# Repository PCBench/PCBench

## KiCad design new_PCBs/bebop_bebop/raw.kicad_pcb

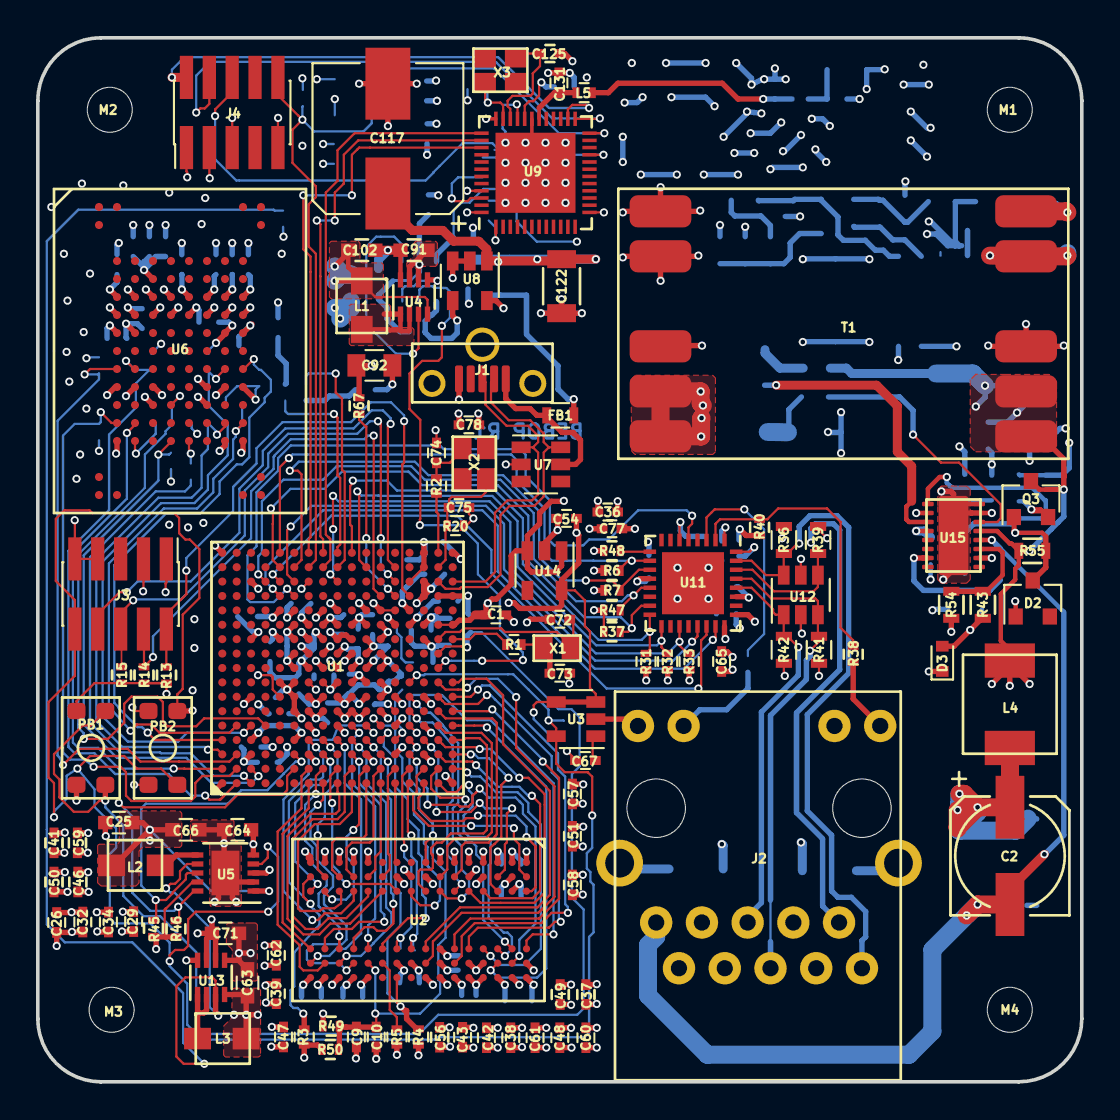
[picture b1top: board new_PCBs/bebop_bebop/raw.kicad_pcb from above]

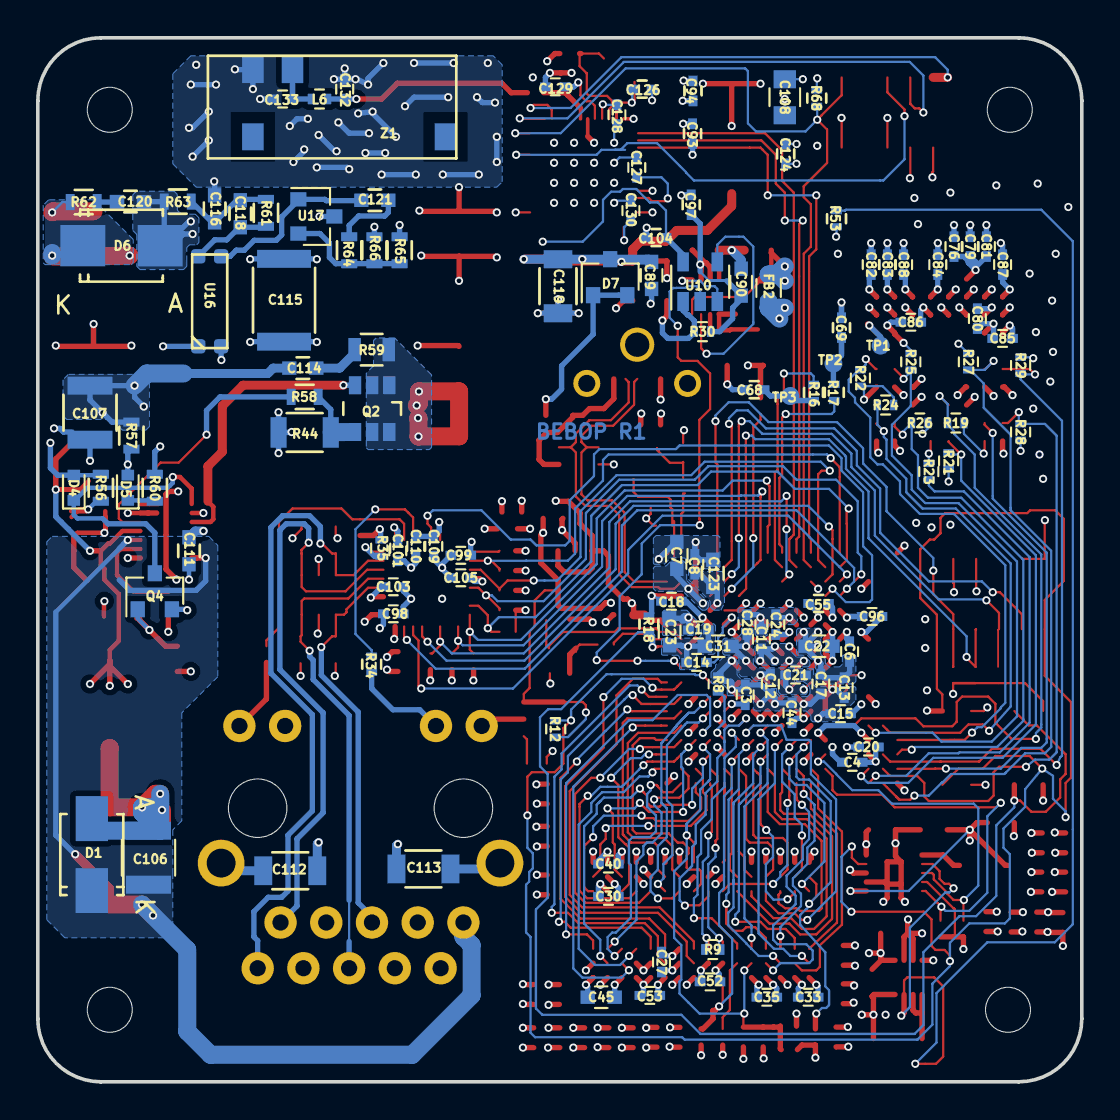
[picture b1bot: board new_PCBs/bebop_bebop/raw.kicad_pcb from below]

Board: 4 copper layers, 58.0 x 58.0 mm, 245 parts (128 on the bottom side), 175 nets.

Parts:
C1, C3, C4, C6, C8, C9, C10, C11, C12, C13, C14, C15, C17, C18, C19, C20, C21, C24, C26, C27, C28, C29, C30, C32, C33, C34, C35, C36, C37, C38, C39, C40, C41, C42, C43, C44, C46, C47, C48, C49, C50, C51, C52, C53, C54, C55, C56, C57, C58, C59, C60, C61, C62, C65, C76, C77, C78, C79, C80, C81, C82, C83, C84, C85, C86, C87, C88, C93, C94, C96, C97, C98, C99, C101, C103, C104, C105, C109, C110, C124, C127: C0402_1u_10Vdc_X5R; C_0402
C2: PCAP_220u_15; c_elec_6.3x7.7
C7, C22, C23, C25, C31, C45: C0603_22u_10Vdc_X5R; C_0603
C63, C64, C66, C71, C91, C102, C123: C0603_10u_10Vdc_X7R; C_0603
C67: C0402_100n_100Vdc_X5R; C_0402
C68, C69: C0402_10n_50Vdc_X7R; C_0402
C72, C73, C74, C75, C125, C126: C0402_15p_100Vdc_C0G; C_0402
C89, C90: C0603_1u_25Vdc_X7R; C_0603
C92: C0805_10u_25Vdc_X7R; C_0805
C106, C107: C1210_1u_100Vdc_X7R; C_1210
C108: C0805_20n_50Vdc_X7R; C_0805
C111: C0603_4u7_10Vdc_X7R; C_0603
C112, C113: C1206_1n5_1000Vdc_X7R; C_1206
C114: C0603_68p_200Vdc_X7R; C_0603
C115: C1812_2n2_250Vac_X7R; C_1812
C116: C0603_1u_10Vdc_X7R; C_0603
C117: PCAP_220u_15; CP_Elec_8x5.4
C118: C0603_33n_16Vdc_X7R; C_0603
C119, C122: C1206_100u_6.3Vdc_X5R; C_1206
C120: C0603_470p_100Vdc_X7R; C_0603
C121: C0603_27n_16Vdc_X7R; C_0603
C128, C129: C0402_100p_25Vdc_C0G; C_0402
C130: C0402_100n_10Vdc_X7R; C_0402
C131: C0402_0p8_25Vdc_C0G_5; C_0402
C132, C133: C0402_0p8_50Vdc_C0G_3; C_0402
D1: SMAJ58A; SMA_Standard
D2: BZX84C8V2LT1G; SOT-23
D3, D4, D5: BAS516,135; D_SOD-523
D6: P6SMB540A_E3_52; SMB_Standard
D7: BAT54C-7-F; SOT-23
FB1, FB2: BL0603_BLM18KG121TN1D; R_0603
J1: 1051330011
J2: 7499210123
J3, J4: FTSH-105-01-F-DV-K
L1, L3: IHLP1212_1u_1; IHLP1212
L2: IHLP1212_3u3_a5; IHLP1212
L4: IHLP2020_3u3_13; IHLP2020
L5: LQG15HN_3n9; L_0402
L6: LQG15HN_2n7; L_0402
M1, M2, M3, M4: MHNP_2.5mm; MH_2.5mm
PB1, PB2: KMR631NGULCLFS; kmr6
Q2: Si3440ADV; TSOT-6-MK06A
Q3: MMBTA42; SOT-23
Q4: 2N7002; SOT-23
R1, R2, R9, R16, R17: R0402_100R; R_0402
R3, R4, R18, R19, R21, R22, R24, R25, R26, R27, R28, R29, R53, R68: R0402_46k40; R_0402
R5, R8: R0402_240R; R_0402
R6, R7, R12, R30, R33, R37, R40, R45, R46, R47, R48: R0402_10k; R_0402
R13, R14, R15, R67: R0402_100k; R_0402
R20: R0402_2M20; R_0402
R23: R0402_22R; R_0402
R31, R32, R49, R50: R0402_1k50; R_0402
R34, R38: R0402_330R; R_0402
R35: R0402_12k10; R_0402
R36, R39, R41, R42: R0603_49R90; R_0603
R43: R0603_10k; R_0603
R44: R1206_0R130; R_1206
R54, R65: R0603_100k; R_0603
R55, R57: R0603_220k; R_0603
R56: R0603_6k80; R_0603
R58: R0603_4k70; R_0603
R59: R0805_100R_126mW; R_0805
R60: R0603_510R; R_0603
R61: R0603_1k; R_0603
R62: R0603_10R; R_0603
R63: R0603_470R; R_0603
R64: R0603_47k; R_0603
R66: R0603_33k20; R_0603
T1: POE60F-50L_; POE60F
TP1, TP2, TP3: TP; TP_1mm
U1: MCIMX6G2AVM07; LFBGA289
U2: MT41K512M16HA-125; BGA-96_pitch0.8mm_dia0.4mm
U3: LP3470M5-3.08; SOT-23-5
U4: MIC23150-SYMT; DFN-8_2x2mm_Pitch0.5mm
U5: LTC3447; DFN-10-1EP_3x3mm_Pitch0.5mm
U6: FEMC004GTTE7-T13-17; 100LBGA_DQ
U7, U12: USBLC6-4; SOT-23-6
U8: NCP360SNAET1G; SOT-23-5
U9: nRF52832; UQFN-48-1EP_6x6mm_Pitch0.4mm
U10: SN74AHC1G08; SOT-23-5
U11: LAN8710; QFN-32-1EP_5x5mm_Pitch0.5mm
U13: MIC23150-55YMT; DFN-8_2x2mm_Pitch0.5mm
U14: NCV551SN33T1G; SOT-23-5
U15: LTC4267IDHC; DHC16
U16: PS2911-1e; PS2911
U17: TL431BSA-7; SOT-23
X1: NX2012SA-32.768K-STD-MUB-1; NX2012
X2: NX2520SA-24.000000MHZ; NX2520
X3: NX2520SA-32.000000MHZ; NX2520
Z1: PRO-OB-440

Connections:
/BLE/BM: U1.G17, U9.39
/BLE/NRF_SWDCLK: J4.4, U9.25
/BLE/NRF_SWDIO: J4.2, U9.26
/BLE/NRF_SWO: J4.6, U9.21
/BLE/RESET_N: J4.10, R68.2, U1.G16, U9.24
/CPU/A0: U1.L5, U2.N3
/CPU/A1: U1.H2, U2.P7
/CPU/A2: U1.K1, U2.P3
/CPU/A3: U1.M2, U2.N2
/CPU/A4: U1.K4, U2.P8
/CPU/A5: U1.L1, U2.P2
/CPU/A6: U1.G2, U2.R8
/CPU/A7: U1.H4, U2.R2
/CPU/A8: U1.J4, U2.T8
/CPU/A9: U1.L2, U2.R3
/CPU/A10: U1.M4, U2.L7
/CPU/A11: U1.K3, U2.R7
/CPU/A12: U1.L4, U2.N7
/CPU/A13: U1.H3, U2.T3
/CPU/A14: U1.G1, U2.T7
/CPU/A15: U1.K5, U2.M7
/CPU/BM0: PB1.2, R18.1, U1.T10
/CPU/DQ0: U1.T4, U2.E3
/CPU/DQ1: U1.U6, U2.F7
/CPU/DQ2: U1.T6, U2.F2
/CPU/DQ3: U1.U7, U2.F8
/CPU/DQ4: U1.U8, U2.H7
/CPU/DQ5: U1.T8, U2.H8
/CPU/DQ6: U1.T5, U2.G2
/CPU/DQ7: U1.U4, U2.H3
/CPU/DQ8: U1.U2, U2.D7
/CPU/DQ9: U1.U3, U2.C3
/CPU/DQ10: U1.U5, U2.C8
/CPU/DQ11: U1.R4, U2.C2
/CPU/DQ12: U1.P5, U2.A7
/CPU/DQ13: U1.P3, U2.B8
/CPU/DQ14: U1.R2, U2.A2
/CPU/DQ15: U1.R1, U2.A3
/CPU/DRAM_CAS_B: U1.J2, U2.K3
/CPU/DRAM_CS0_B: U1.N2, U2.L2
/CPU/DRAM_DQM0: U1.T7, U2.E7
/CPU/DRAM_DQM1: U1.T3, U2.D3
/CPU/DRAM_ODT0: U1.N1, U2.K1
/CPU/DRAM_RAS_B: U1.M5, U2.J3
/CPU/DRAM_RESET: R3.1, U1.G4, U2.T2
/CPU/DRAM_SDBA0: U1.M1, U2.M2
/CPU/DRAM_SDBA1: U1.H1, U2.N8
/CPU/DRAM_SDBA2: U1.K2, U2.M3
/CPU/DRAM_SDCKE0: R4.1, U1.M3, U2.K9
/CPU/DRAM_SDCLK0_N: R9.1, U1.P2, U2.K7
/CPU/DRAM_SDCLK0_P: R9.2, U1.P1, U2.J7
/CPU/DRAM_SDQS0_N: U1.P7, U2.G3
/CPU/DRAM_SDQS0_P: U1.P6, U2.F3
/CPU/DRAM_SDQS1_N: U1.T2, U2.B7
/CPU/DRAM_SDQS1_P: U1.T1, U2.C7
/CPU/DRAM_SDWE_B: U1.J1, U2.L3
/CPU/DRAM_VREFDQ: C9.2, C10.1, R49.2, R50.1, U1.P4, U2.H1, U2.M8
/CPU/DRAM_ZQ0: R5.1, U2.L8
/CPU/DRAM_ZQPAD: R8.1, U1.N4
/CPU/DRX: R16.2, U1.J16
/CPU/DTX: R17.2, U1.J17
/CPU/I2C2_SCL: R45.2, U1.F3, U5.8
/CPU/I2C2_SDA: R46.2, U1.F2, U5.10
/CPU/JTAG_TCK: J3.4, R14.2, U1.M14
/CPU/JTAG_TDI: J3.8, U1.N16
/CPU/JTAG_TDO: J3.6, R15.2, U1.N15
/CPU/JTAG_TMS: J3.2, R13.2, U1.P14
/CPU/JTAG_TRST_N: R67.2, U1.N14
/CPU/NVCC_PLL: C8.1, C123.1, U1.P13
/CPU/P3V3_PG: R53.2, U5.7, U13.3
/CPU/POWER_REQ: U1.T9, U10.2
/CPU/RST_N: J3.10, PB2.2, R12.2, U1.P8, U3.5, U5.4
/CPU/UART3_RX_DATA: U1.H16, U9.37
/CPU/UART3_TX_DATA: U1.H17, U9.38
/CPU/VDD_ARM_CAP: C6.1, C13.1, C17.1, C22.1, U1.G9, U1.G10, U1.G11, U1.H11
/CPU/VDD_HIGH_CAP: C3.1, C7.1, U1.N6, U1.R14, U1.R15
/CPU/VDD_SNVS_CAP: C14.1, U1.N12
/CPU/VDD_SOC_CAP: C12.1, C21.1, C24.1, C28.1, C31.1, U1.G8, U1.H8, U1.J8, U1.J11, U1.K8, U1.K11, U1.L8, U1.L9, U1.L10, U1.L11
/CPU/VDD_USB_CAP: C19.1, C23.1, U1.R12
/CPU/eMMC_CLK: R23.2, U1.C1
/CPU/eMMC_CLK_2: R23.1, U6.P6
/CPU/eMMC_CMD: R21.2, U1.C2, U6.P5
/CPU/eMMC_D0: R29.2, U1.B3, U6.K2
/CPU/eMMC_D1: R28.2, U1.B2, U6.N2
/CPU/eMMC_D2: R27.2, U1.B1, U6.K3
/CPU/eMMC_D3: U1.A2, U6.N3
/CPU/eMMC_D4: R26.2, U1.A3, U6.N8
/CPU/eMMC_D5: R25.2, U1.C5, U6.K8
/CPU/eMMC_D6: R24.2, U1.B5, U6.N9
/CPU/eMMC_D7: R22.2, U1.A4, U6.K9
/CPU/eMMC_RST_N: R19.2, U1.D5, U6.M5
/CPU/eMMC_VDDIM: C76.1, C79.1, C81.1, U6.E4
/CR: C109.1, C110.1, U11.6
/ENET_CLK: U1.F14, U11.5
/ENET_CRS_DV: R37.2, U1.E16, U11.15
/ENET_MDC: R32.1, U1.L16, U11.17
/ENET_MDIO: R31.1, U1.K17, U11.16
/ENET_RST_N: R33.1, U1.J15, U11.19
/ENET_RXD0: R7.2, U1.F16, U11.11
/ENET_RXD1: R6.2, U1.E17, U11.10
/ENET_RXER: R47.2, U1.D15, U11.13
/ENET_TXD0: U1.E15, U11.22
/ENET_TXD1: U1.E14, U11.23
/ENET_TXEN: U1.F15, U11.21
/P3V3_EN: U4.3, U10.4
/PoE/NGATE: Q2.3, U15.3
/PoE/PVCC: C111.2, D5.2, Q3.2, R54.1, R56.2, R57.2, U15.4
/PoE/SENSE: R58.2, U15.14
/PoE/VPORTN: C2.2, C106.1, D1.1, J2.10, U15.7, U15.12
/PoE/VPORTP: C2.1, C106.2, D1.3, J2.9, L4.1
/USB_D_N: J1.2, U1.T15, U7.6
/USB_D_P: J1.3, U1.U15, U7.1
/USB_VBUS: FB1.1, J1.1, U7.5
/USB_VBUS_2: C89.1, C117.1, C119.1, C120.1, C122.1, D6.2, D7.3, R63.1, R65.1, U8.1
GND: C1.2, C3.2, C4.2, C6.2, C7.2, C8.2, C10.2, C11.2, C12.2, C13.2, C14.2, C15.2, C17.2, C18.2, C19.2, C20.2, C21.2, C22.2, C23.2, C24.2, C25.2, C26.2, C27.2, C28.2, C29.2, C30.2, C31.2, C32.2, C33.2, C34.2, C35.2, C36.2, C37.2, C38.2, C39.2, C40.2, C41.2, C42.2, C43.2, C44.2, C45.2, C46.2, C47.2, C48.2, C49.2, C50.2, C51.2, C52.2, C53.2, C54.2, C55.2, C56.2, C57.2, C58.2, C59.2, C60.2, C61.2, C62.2, C63.2, C64.2, C65.2, C66.2, C67.2, C68.2, C69.2, C71.2, C72.2, C73.2, C74.2, C75.2, C76.2, C77.2, C78.2, C79.2, C80.2, C81.2, C82.2, C83.2, C84.2, C85.2, C86.2, C87.2, C88.2, C89.2, C90.2, C91.2, C92.2, C93.2, C94.2, C96.2, C97.2, C98.2, C99.2, C101.2, C102.2, C103.2, C104.2, C105.2, C108.2, C109.2, C110.2, C112.2, C113.2, C115.1, C116.2, C117.2, C119.2, C122.2, C123.2, C124.2, C125.1, C126.1, C127.2, C128.2, C129.2, C130.2, C131.2, C132.2, C133.2, J1.5, J1.6, J1.7, J1.8, J2.12, J2.14, J3.3, J3.7, J3.9, J4.3, J4.5, J4.9, PB2.1, R3.2, R4.2, R5.2, R8.2, R18.2, R20.2, R33.2, R35.2, R40.2, R50.2, R66.2, T1.7, T1.8, TP1.1, U1.A1, U1.A17, U1.C3, U1.C7, U1.C11, U1.C15, U1.E8, U1.E11, U1.F6, U1.F7, U1.F8, U1.F9, U1.F10, U1.F11, U1.F12, U1.G3, U1.G5, U1.G7, U1.G12, U1.G15, U1.H7, U1.H12, U1.J5, U1.J7, U1.J12, U1.K7, U1.K12, U1.L3, U1.L7, U1.L12, U1.M7, U1.M8, U1.M9, U1.M10, U1.M11, U1.M12, U1.N3, U1.N5, U1.N7, U1.P15, U1.R3, U1.R5, U1.R7, U1.R11, U1.R16, U1.R17, U1.T14, U1.U1, U1.U14, U1.U17, U2.A9, U2.B1, U2.B3, U2.B9, U2.D1, U2.D8, U2.E1, U2.E2, U2.E8, U2.F9, U2.G1, U2.G8, U2.G9, U2.J2, U2.J8, U2.M1, U2.M9, U2.P1, U2.P9, U2.T1, U2.T9, U3.2, U4.5, U4.8, U5.2, U5.11, U6.G2, U6.G3, U6.G4, U6.G5, U6.G6, U6.G7, U6.G8, U6.G9, U6.H2, U6.H9, U6.L3, U6.L8, U6.M4, U6.M7, U6.P2, U6.P9, U7.2, U8.2, U8.3, U9.31, U9.45, U9.49, U10.3, U11.24, U11.25, U11.33, U12.2, U13.5, U13.8, U14.2, U17.3, Z1.1
GND_POWER: C107.1, C111.1, C115.2, D2.1, D3.1, Q4.2, R44.2, T1.3, U15.2, U15.10, U15.15, U15.16, U15.17, U16.2
unnamed: C67.1, U3.1
unnamed: C68.1, R16.1, TP3.1
unnamed: C69.1, R17.1, TP2.1
unnamed: C72.1, U1.T11, X1.1
unnamed: C73.1, R1.2, X1.3
unnamed: C74.1, R2.2, X2.1
unnamed: C75.1, R20.1, U1.T16, X2.3
unnamed: C102.1, FB2.1, L1.2, U4.4
unnamed: C107.2, C114.1, L4.2, Q3.3, R55.2, R57.1, T1.1, T1.2, U15.13
unnamed: C112.1, J2.15
unnamed: C113.1, J2.16
unnamed: C114.2, R59.2
unnamed: C116.1, C118.1, R61.1, R63.2
unnamed: C118.2, R61.2, U16.4
unnamed: C120.2, R62.2
unnamed: C121.1, R64.2
unnamed: C121.2, U16.3, U17.1
unnamed: C125.2, U9.34, X3.3
unnamed: C126.2, U9.35, X3.1
unnamed: C127.1, U9.46
unnamed: C128.1, U9.33
unnamed: C129.1, U9.32
unnamed: C130.1, U9.1
unnamed: C131.1, L5.1, U9.30
unnamed: C132.1, L5.2, L6.1
unnamed: C133.1, L6.2, Z1.2
unnamed: D2.3, Q3.1, R55.1
unnamed: D3.2, Q4.1, R43.1
unnamed: D4.1, Q4.3, U15.1
unnamed: D4.2, R56.1, U16.1
unnamed: D5.1, R60.2
unnamed: D6.1, R62.1, T1.5, T1.6
unnamed: D7.1, D7.2, FB1.2
unnamed: J2.1, R36.2, U11.31, U12.6
unnamed: J2.2, R39.2, U11.30, U12.4
unnamed: J2.5, R41.2, U11.29, U12.3
unnamed: J2.6, R42.2, U11.28, U12.1
unnamed: J2.11, R38.2
unnamed: J2.13, R34.2
unnamed: L1.1, U4.1, U4.2
unnamed: L2.2, U5.6
unnamed: L3.2, U13.1, U13.2
unnamed: Q2.1, Q2.2, Q2.5, Q2.6, R59.1, T1.11, T1.12
unnamed: Q2.4, R44.1, R58.1
unnamed: R1.1, U1.U11
unnamed: R2.1, U1.T17
unnamed: R30.2, U8.4, U10.1
unnamed: R34.1, U11.3
unnamed: R35.1, U11.32
unnamed: R38.1, R40.1, U11.2
unnamed: R43.2, R54.2, U15.11
unnamed: R48.2, U11.9
unnamed: R60.1, T1.10
unnamed: R64.1, R65.2, R66.1, U17.2
P1V4: C4.1, C11.1, C15.1, C20.1, C25.1, C66.1, L2.1, U1.H9, U1.H10, U1.J9, U1.J10, U1.K9, U1.K10, U5.1
P1V35: C9.1, C27.1, C30.1, C33.1, C35.1, C37.1, C38.1, C39.1, C40.1, C42.1, C43.1, C44.1, C45.1, C47.1, C48.1, C49.1, C51.1, C52.1, C53.1, C56.1, C57.1, C58.1, C60.1, C61.1, C62.1, C63.1, L3.1, R49.1, U1.G6, U1.H6, U1.J6, U1.K6, U1.L6, U1.M6, U2.A1, U2.A8, U2.B2, U2.C1, U2.C9, U2.D2, U2.D9, U2.E9, U2.F1, U2.G7, U2.H2, U2.H9, U2.K2, U2.K8, U2.N1, U2.N9, U2.R1, U2.R9, U13.4
P3V3: C26.1, C29.1, C32.1, C34.1, C36.1, C41.1, C46.1, C50.1, C55.1, C59.1, C64.1, C65.1, C71.1, C77.1, C78.1, C80.1, C82.1, C83.1, C84.1, C85.1, C86.1, C87.1, C88.1, C92.1, C93.1, C94.1, C96.1, C98.1, C99.1, C101.1, C103.1, C105.1, C108.1, C124.1, FB2.2, J2.3, J2.4, J3.1, J4.1, PB1.1, R6.1, R7.1, R13.1, R14.1, R15.1, R19.1, R21.1, R22.1, R24.1, R25.1, R26.1, R27.1, R28.1, R29.1, R31.2, R32.2, R36.1, R37.1, R39.1, R41.1, R42.1, R45.1, R46.1, R47.1, R48.1, R53.1, R67.1, R68.1, U1.C4, U1.E7, U1.E13, U1.F4, U1.F13, U1.H13, U1.J13, U1.L13, U1.M13, U1.N13, U5.3, U5.5, U5.9, U6.F2, U6.F3, U6.F4, U6.F5, U6.F6, U6.F7, U6.F8, U6.F9, U6.H3, U6.H8, U6.L2, U6.L4, U6.L7, U6.L9, U6.P3, U6.P8, U9.13, U9.36, U9.48, U11.1, U11.12, U11.27, U12.5, U13.6, U13.7
P3V3_PERM: C18.1, C54.1, C104.1, R12.1, U1.P12, U3.3, U3.4, U10.5, U14.5
P5V0: C1.1, C90.1, C91.1, C97.1, R30.1, U1.T12, U1.U12, U4.6, U4.7, U8.5, U14.1, U14.3

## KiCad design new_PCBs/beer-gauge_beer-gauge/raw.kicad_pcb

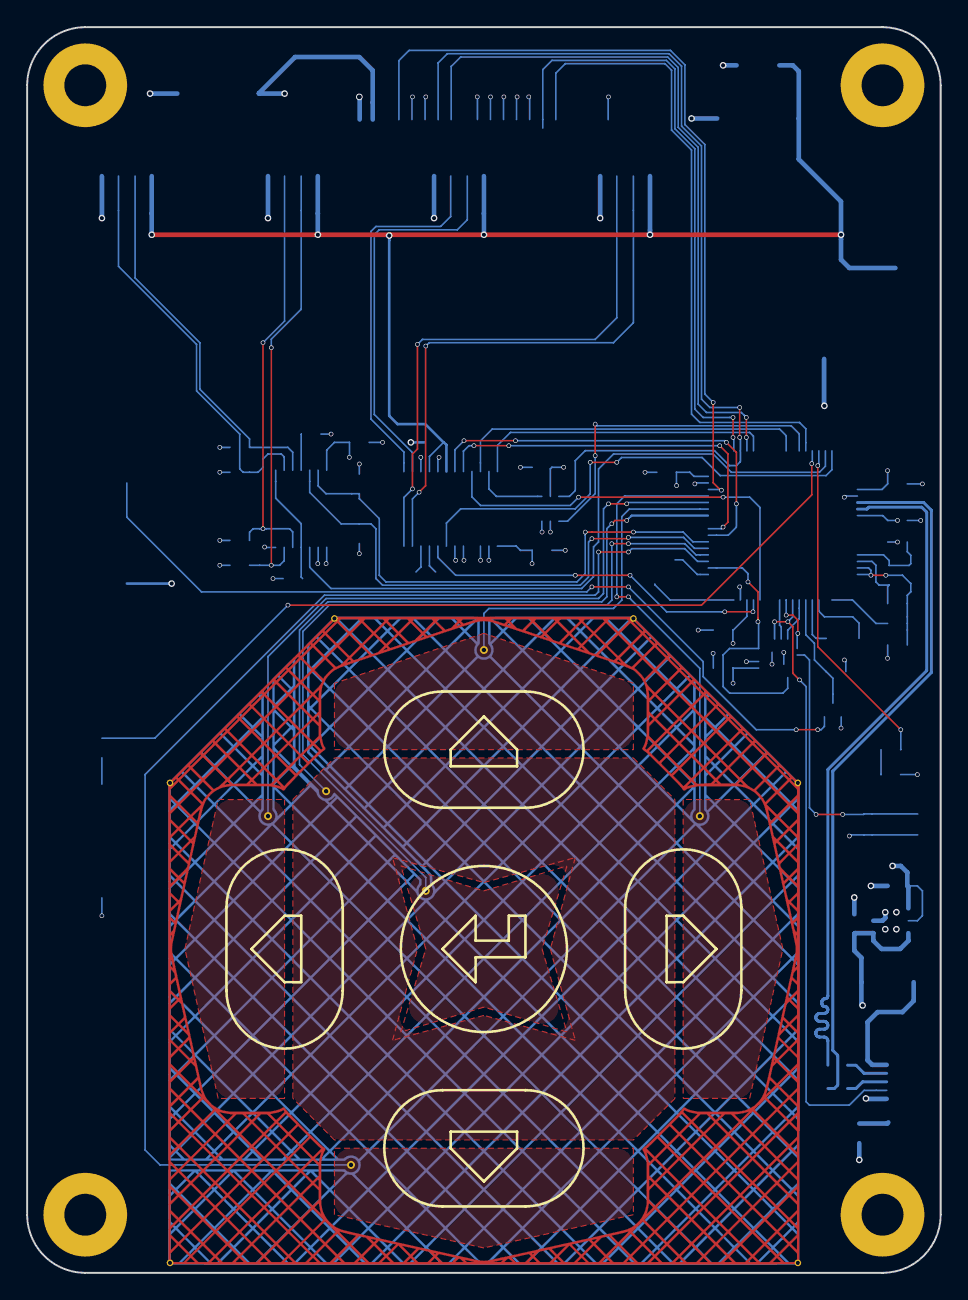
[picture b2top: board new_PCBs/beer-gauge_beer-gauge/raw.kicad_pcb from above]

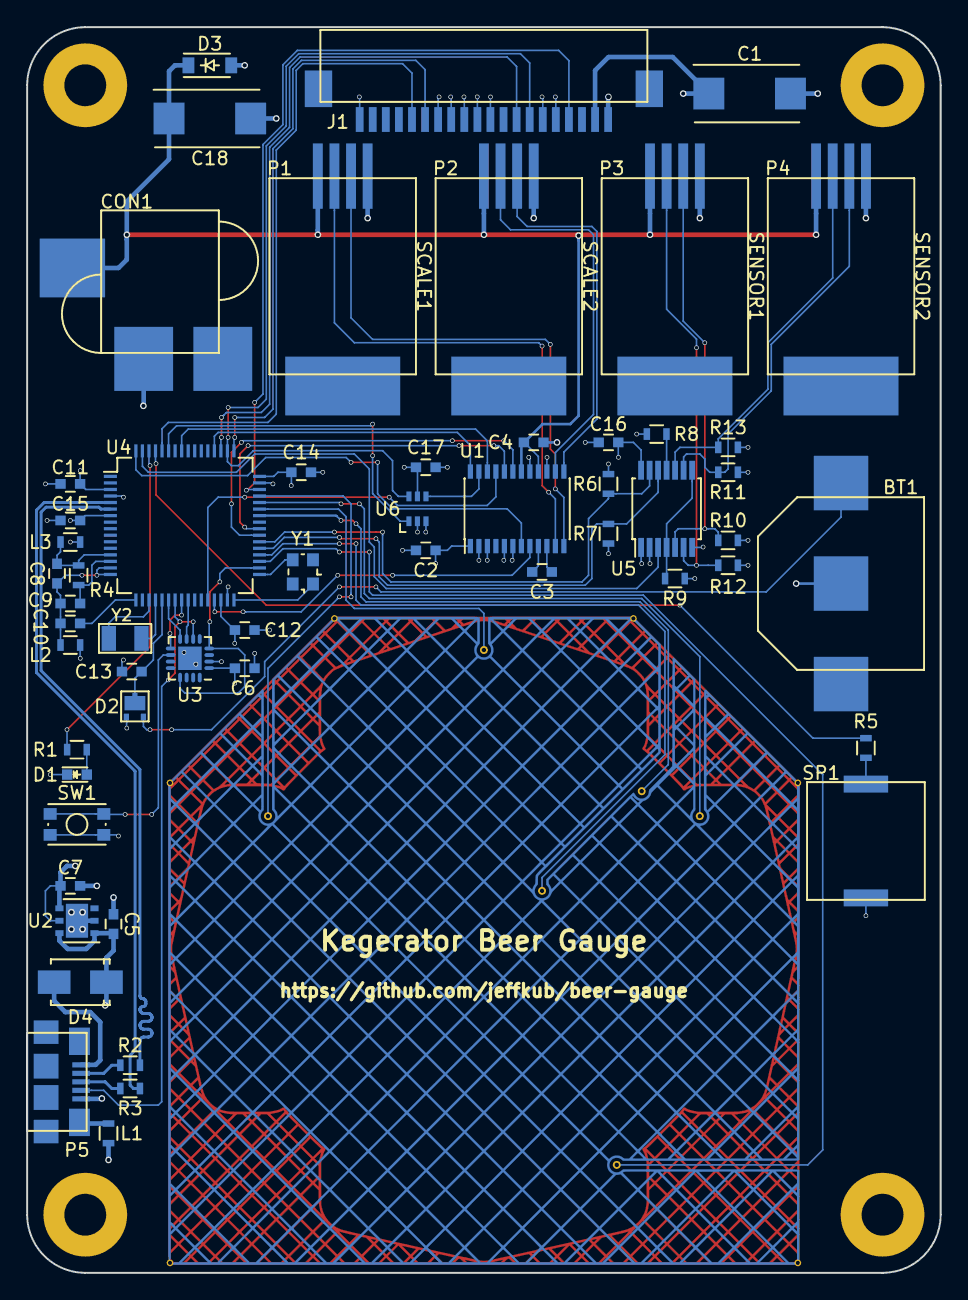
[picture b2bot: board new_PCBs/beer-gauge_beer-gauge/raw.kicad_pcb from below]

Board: 4 copper layers, 69.8 x 95.2 mm, 62 parts (56 on the bottom side), 64 nets.

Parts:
BT1: Battery; BK-885
C1: 220u; TantalC_SizeD_EIA-7343_Reflow
C2, C3, C4, C6, C9, C10, C11, C12, C13, C14, C16, C17: 0.1u; C_0603
C5, C7, C8, C15: 2.2u; C_0603
C18: 100u; TantalC_SizeD_EIA-7343_Reflow
CON1: BARREL_JACK; PJ-070AH-SMT
D1: LED; LED_0603
D2: PMEG4010CPA; SOT1061
D3: DDZ6V2B; SOD-123
D4: S1B; SMA_Standard
J1: OLED_MODULE; 0522712069
L1, L3: 600 Ohm/100 MHz; R_0603
L2: 600 Ohm/100 Mhz; R_0603
P1, P2, P3, P4: CONN_01X04; 0855135016
P5: USB_OTG; 10118192
R1, R4, R5: 470; R_0603
R2, R3: 33; R_0603
R6, R7, R8, R9, R10, R11, R12, R13: 4.7k; R_0603
SP1: PIEZO; PKMCS
SW1: SW_PUSH; SW_SPST_KMR2
U1: ADS1232; TSSOP-24_4.4x7.8mm_Pitch0.65mm
U2: LP38691; DFN-6-1EP_3x3mm_Pitch0.95mm
U3: MKL02Z32; QFN-16-1EP_3x3mm_Pitch0.5mm
U4: MK20DX256VLH7; LQFP-64_10x10mm_Pitch0.5mm
U5: TCA9543A; TSSOP-14_4.4x5mm_Pitch0.65mm
U6: SN74LVC1G58; SC-70-6
W1, W2, W3, W4, W5, W6: TEST_1P; PadVia
Y1: 16 MHz; Crystal_SMD_2520_4Pads
Y2: 32.768 kHz; ABS07

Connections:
+3V3: C1.1, C2.1, C6.1, C7.1, C11.1, C12.1, C14.1, C15.1, C16.1, C17.1, D2.2, J1.2, L3.1, R6.1, R7.1, R8.1, R9.1, R10.1, R11.1, R12.1, R13.1, U1.1, U2.4, U2.5, U3.1, U4.3, U4.7, U4.30, U4.48, U5.14, U6.5
+5V: C4.1, C5.1, C18.1, CON1.1, D3.1, D4.1, P1.1, P2.1, P3.1, P4.1, U1.16, U1.18, U2.1, U2.6
/Teensy/0: U1.19, U4.39
/Teensy/1: U1.20, U4.40
/Teensy/2: U1.22, U4.57
/Teensy/3: U1.21, U4.28
/Teensy/4: U1.8, U4.29
/Teensy/5: U1.7, U4.64
/Teensy/6: R5.2, U4.61
/Teensy/7: U4.59, U6.1
/Teensy/8: J1.16, U4.60
/Teensy/9: J1.4, U4.46
/Teensy/10: J1.15, U4.49
/Teensy/11: J1.8, U4.51
/Teensy/12: U1.24, U4.52
/Teensy/13: J1.7, U4.50, U6.6
/Teensy/15/A1: U4.43, W1.1
/Teensy/16/A2: U4.35, W2.1
/Teensy/17/A3: U4.36, W5.1
/Teensy/18/A4: R6.2, U4.38, U5.13
/Teensy/19/A5: R7.2, U4.37, U5.12
/Teensy/20/A6: R1.1, U4.62
/Teensy/21/A7: U4.63, U5.3
/Teensy/22/A8: U4.44, W3.1
/Teensy/23/A9: U4.45, W4.1
/Teensy/25: U4.42, W6.1
/Teensy/AREF: C9.1, R4.1, U4.14
/Teensy/ID: P5.4, U3.6, U4.23
/Teensy/RESET_B: U3.4, U3.13, U4.34
/Teensy/SWD_CLK: U3.8, U4.22
/Teensy/SWD_DIO: U3.7, U4.25
/Teensy/USB_D+: R3.1, U4.5
/Teensy/USB_D-: R2.1, U4.6
GND: BT1.2, C1.2, C2.2, C4.2, C5.2, C6.2, C7.2, C11.2, C12.2, C13.2, C14.2, C15.2, C16.2, C17.2, C18.2, CON1.2, D1.1, D3.2, J1.1, J1.5, J1.6, J1.10, J1.11, J1.12, J1.13, J1.14, J1.20, L1.2, L2.1, P1.4, P2.4, P3.4, P4.4, P5.5, SP1.2, SW1.1, U1.2, U1.3, U1.5, U1.6, U1.15, U1.17, U2.2, U2.7, U3.2, U3.17, U4.4, U4.31, U4.47, U5.1, U5.2, U5.7, U6.2, U6.3
unnamed: BT1.1, D2.1
unnamed: C3.1, U1.9
unnamed: C3.2, U1.10
unnamed: C8.1, L3.2, R4.2, U4.13
unnamed: C10.1, U4.17
unnamed: C8.2, C9.2, C10.2, L2.2, U4.15, U4.16
unnamed: C13.1, D2.3, U4.21
unnamed: D1.2, R1.2
unnamed: D4.2, P5.1
unnamed: L1.1, P5.6
unnamed: P1.2, U1.11
unnamed: P1.3, U1.12
unnamed: P2.2, U1.14
unnamed: P2.3, U1.13
unnamed: P3.2, R12.2, U5.6
unnamed: P3.3, R10.2, U5.5
unnamed: P4.2, R13.2, U5.10
unnamed: P4.3, R11.2, U5.9
unnamed: P5.2, R2.2
unnamed: P5.3, R3.2
unnamed: R5.1, SP1.1
unnamed: R8.2, U5.11
unnamed: R9.2, U5.4, U5.8
unnamed: SW1.2, U3.10
unnamed: U1.23, U6.4
unnamed: U3.9, U4.24
unnamed: U4.19, Y2.1
unnamed: U4.20, Y2.2
unnamed: U4.32, Y1.1
unnamed: U4.33, Y1.2

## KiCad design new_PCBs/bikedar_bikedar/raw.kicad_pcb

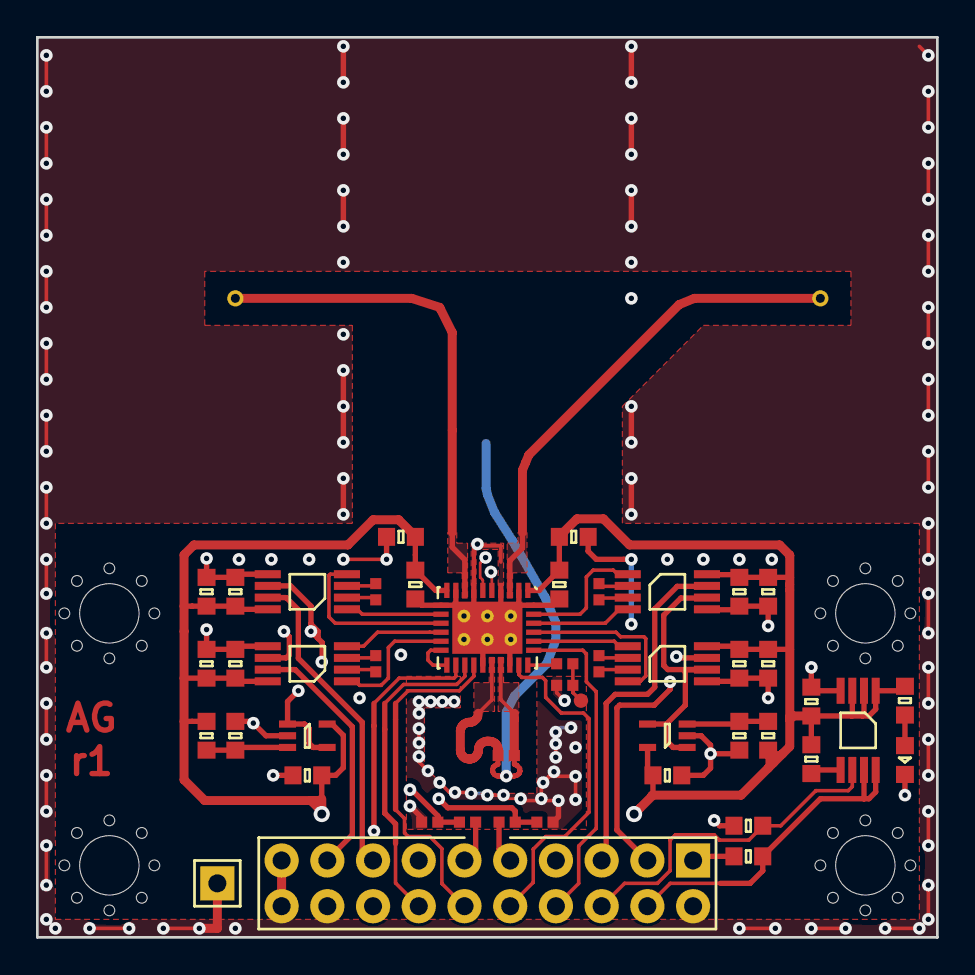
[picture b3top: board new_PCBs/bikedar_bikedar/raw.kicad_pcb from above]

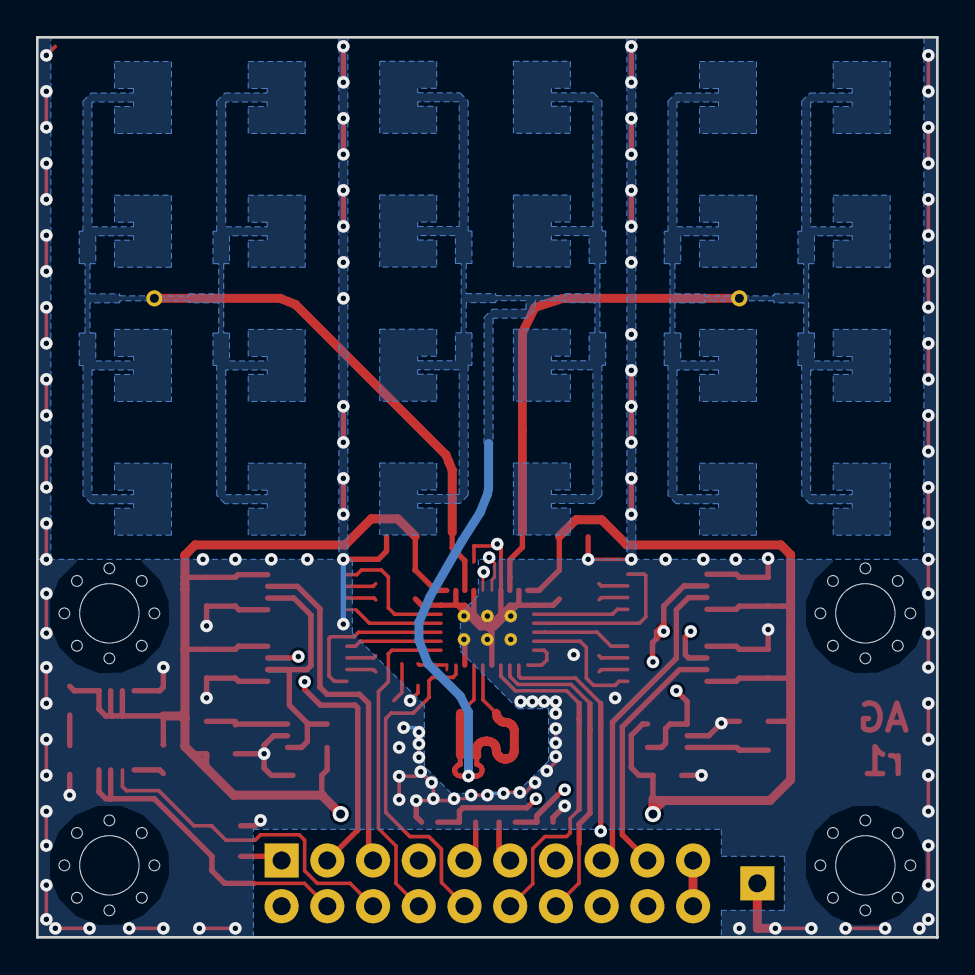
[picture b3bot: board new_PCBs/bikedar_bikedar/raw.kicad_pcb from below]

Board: 4 copper layers, 50.0 x 50.0 mm, 52 parts (2 on the bottom side), 45 nets.

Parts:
AE2, AE3: X0
C1, C3, C7, C18: 1µ; 0603
C2: 1n; 0603
C4, C15, C19, C20: 10µ; 0603
C5, C6: 100n; 0402
C8, C10, C11, C12, C13, C14, C16, C17: 100n; 0603
C9: 1n; 0402
D1: LED; 0603-LED
IC1: ADP3335; MSOP-8
IC2: BGT24MTR12; QFN-32-BGT24MTR
IC3, IC8: AD8541; SC-70-5
IC4, IC5, IC6, IC7: AD8226; MSOP-8
J1: CONN_02x10; DIL-254P-20
R1, R2, R13: 100; 0402
R3: 50; 0402
R4, R5, R10, R11, R12: 10k; 0603
R6, R7, R8, R9: 5k49; 0402
R14: 1k; 0603
TP1: TESTPAD
TP2: TESTPAD; SIL-254P-01
X1, X2, X3, X4: M3_MOUNT

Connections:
3v3: C2.2, C3.1, C4.1, C7.1, C8.1, C10.1, C11.1, C12.1, C13.1, C14.1, C15.1, C16.1, C17.1, C18.1, C19.1, C20.1, IC1.1, IC1.2, IC1.3, IC2.1, IC2.10, IC3.5, IC4.8, IC5.8, IC6.8, IC7.8, IC8.5, R4.1, R11.1, R14.1
/ANA: IC2.25, J1.10
/CLK: IC2.19, J1.14
/COARSE: J1.11, R2.1
/FINE: J1.9, R1.1
/FREQ: IC2.27, J1.8
/IFI1: IC4.7, J1.3
/IFI1_N: IC2.28, IC4.1
/IFI1_P: IC2.29, IC4.4
/IFI2: IC6.7, J1.17
/IFI2_N: IC2.15, IC6.1
/IFI2_P: IC2.14, IC6.4
/IFQ1: IC5.7, J1.5
/IFQ1_N: IC2.31, IC5.1
/IFQ1_P: IC2.30, IC5.4
/IFQ2: IC7.7, J1.15
/IFQ2_N: IC2.12, IC7.1
/IFQ2_P: IC2.13, IC7.4
/RX1: AE2.1, IC2.3
/RX2: AE3.1, IC2.8
/SI: IC2.20, J1.12
/TX: IC2.22, IC2.23, R13.1, R13.2
/VREF1: IC3.1, IC3.4, IC4.6, IC5.6
/VREF2: IC6.6, IC7.6, IC8.1, IC8.4
/~CS: IC2.18, J1.16
/~SD: IC1.6, J1.6, R10.1
GND: C1.2, C3.2, C4.2, C5.2, C6.1, C7.2, C8.2, C10.2, C11.2, C12.2, C13.2, C14.2, C15.2, C16.2, C17.2, C18.2, C19.2, C20.2, D1.1, IC1.4, IC2.2, IC2.4, IC2.7, IC2.9, IC2.11, IC2.21, IC2.24, IC2.32, IC2.EP, IC3.2, IC4.5, IC5.5, IC6.5, IC7.5, IC8.2, J1.1, J1.2, J1.7, J1.13, J1.18, J1.19, J1.20, R3.1, R5.2, R10.2, R12.2, TP2.1
unnamed: C2.1, IC1.5
unnamed: C5.1, IC2.5, R1.2
unnamed: C6.2, IC2.6, R2.2
unnamed: C9.1, R3.2, TP1.1
unnamed: C9.2, IC2.26
unnamed: D1.2, R14.2
unnamed: IC2.16, IC2.17
unnamed: IC3.3, R4.2, R5.1
unnamed: IC4.2, R6.2
unnamed: IC4.3, R6.1
unnamed: IC5.2, R7.2
unnamed: IC5.3, R7.1
unnamed: IC6.2, R8.2
unnamed: IC6.3, R8.1
unnamed: IC7.2, R9.2
unnamed: IC7.3, R9.1
unnamed: IC8.3, R11.2, R12.1
VBATT: C1.1, IC1.7, IC1.8, J1.4

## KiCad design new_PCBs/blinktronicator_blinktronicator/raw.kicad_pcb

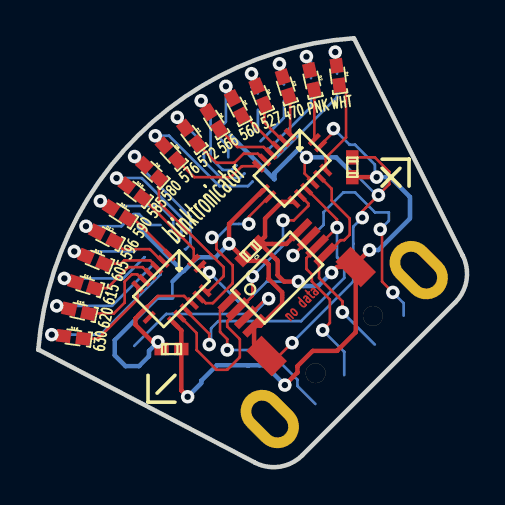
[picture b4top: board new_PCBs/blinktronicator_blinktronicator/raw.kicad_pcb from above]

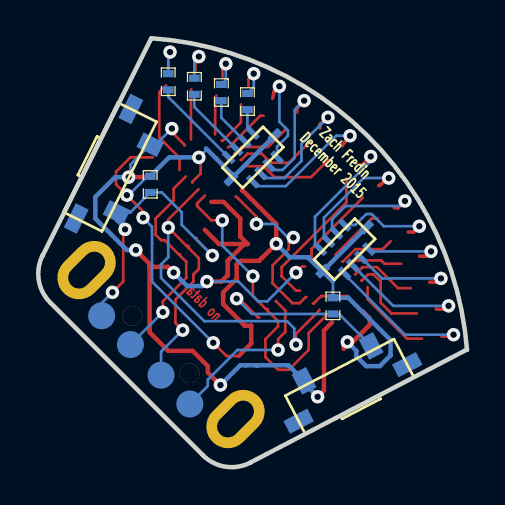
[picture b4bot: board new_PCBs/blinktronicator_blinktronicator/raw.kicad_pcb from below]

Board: 2 copper layers, 23.8 x 23.8 mm, 37 parts (14 on the bottom side), 45 nets.

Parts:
C1, C2, C3: 0.1; c_0402
CONN1: USB_PLUG; USBplug
D1: WHT; LED-0402
D2: PNK; LED-0402
D3: 470nm; LED-0402
D4: 527nm; LED-0402
D5: 560nm; LED-0402
D6: 566nm; LED-0402
D7: 572nm; LED-0402
D8: 576nm; LED-0402
D9: 580nm; LED-0402
D10: 585nm; LED-0402
D11: 590nm; LED-0402
D12: 596nm; LED-0402
D13: 605nm; LED-0402
D14: 615nm; LED-0402
D15: 620nm; LED-0402
D16: 630nm; LED-0402
P3: RST; PAD_1-5mm
P4: SCK; PAD_1-5mm
P5: MISO; PAD_1-5mm
P6: MOSI; PAD_1-5mm
R1, R4, R5, R6: R; SM0402
R2, R3: 10k; SM0402
RN1, RN2: EXB-D10C680J; RN-EXBD
SW2, SW3: SW_PUSH; TL3330AF130QG
U1: ATTINY85-S; tssop-8
U3, U4: 74HC595; DHVQFN16

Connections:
D1: R6.2, RN1.7
D2: R4.2, RN1.8
D3: R5.2, RN1.9
D4: R1.2, RN1.10
D5: D5.2, RN1.2
D6: D6.2, RN1.3
D7: D7.2, RN1.4
D8: D8.2, RN1.5
D9: D9.2, RN2.7
D10: D10.2, RN2.8
D11: D11.2, RN2.9
D12: D12.2, RN2.10
D13: D13.2, RN2.2
D14: D14.2, RN2.3
D15: D15.2, RN2.4
D16: D16.2, RN2.5
GND: C1.1, C2.1, C3.1, CONN1.4, R2.2, R3.2, RN1.1, RN1.6, RN2.1, RN2.6, U1.4, U3.8, U3.13, U4.8, U4.13
unnamed: D2.1, U3.1
unnamed: D1.1, U3.15
unnamed: D4.2, R1.1
unnamed: D3.2, R5.1
unnamed: D2.2, R4.1
unnamed: D1.2, R6.1
unnamed: P3.1, U1.1
unnamed: D5.1, U3.4
unnamed: D8.1, U3.7
unnamed: D7.1, U3.6
unnamed: D6.1, U3.5
unnamed: D4.1, U3.3
unnamed: D3.1, U3.2
unnamed: P6.1, U1.5, U3.14
unnamed: U1.2, U3.11, U4.11
unnamed: U3.9, U4.14
unnamed: P5.1, U1.6, U3.12, U4.12
unnamed: D16.1, U4.7
unnamed: D15.1, U4.6
unnamed: D14.1, U4.5
unnamed: D13.1, U4.4
unnamed: D9.1, U4.15
unnamed: D12.1, U4.3
unnamed: D11.1, U4.2
unnamed: D10.1, U4.1
unnamed: R3.1, SW3.2, U1.3
unnamed: P4.1, R2.1, SW2.2, U1.7
VCC: C1.2, C2.2, C3.2, CONN1.1, SW2.1, SW3.1, U1.8, U3.10, U3.16, U4.10, U4.16
